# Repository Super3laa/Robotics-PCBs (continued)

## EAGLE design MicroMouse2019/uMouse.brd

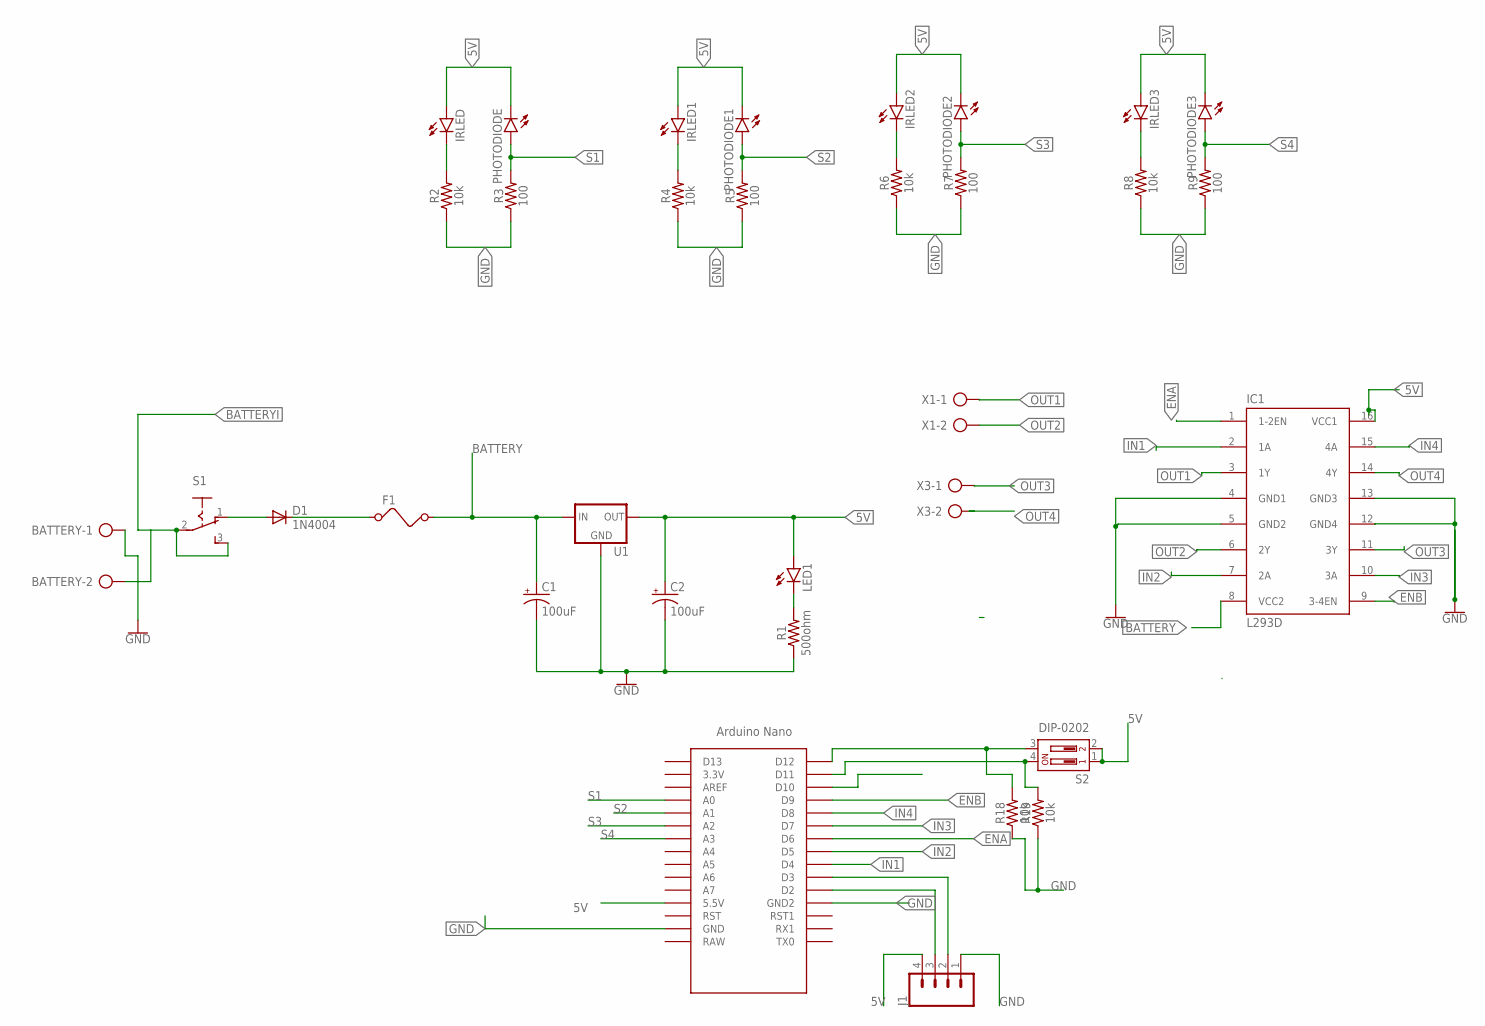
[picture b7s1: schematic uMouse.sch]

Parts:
BATTERY: AK500/2-H
C1, C2: 100uF; CPOL-RADIAL-2.5MM-6.5MM
D1: 1N4004; DO41-10
F1: FUSE
IC1: L293D; DIL16
IRLED, IRLED1, IRLED2, IRLED3: LED5MM
J1: CONN_04; 1X04
LED1: LED3MM
PHOTODIODE, PHOTODIODE1, PHOTODIODE2, PHOTODIODE3: LED5MM
R1: 500ohm; AXIAL-0.3
R2, R4, R6, R8, R18, R19: 10k; AXIAL-0.3
R3, R5, R7, R9: 100; AXIAL-0.3
S1: 255SB
S2: DIP-0202; DIPSWITCH-02
U1: 78XXS
U$2: NANO
X1, X3: AK500/2-H

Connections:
5V: C2.1 (+), IC1.16 (VCC1), IRLED.A, IRLED1.A, IRLED2.A, IRLED3.A, J1.4, LED1.A, PHOTODIODE.K (C), PHOTODIODE1.K (C), PHOTODIODE2.K (C), PHOTODIODE3.K (C), S2.1, S2.2, U1.OUT, U$2.5V (5.5V)
BATTERY: C1.1 (+), F1.2, IC1.8 (VCC2), U1.IN
BATTERYI: BATTERY.2, S1.2, S1.3 (S)
ENA: IC1.1 (1-2EN), U$2.D6
ENB: IC1.9 (3-4EN), U$2.D9
GND: BATTERY.1, C1.2 (-), C2.2 (-), IC1.4 (GND1), IC1.5 (GND2), IC1.12 (GND4), IC1.13 (GND3), J1.1, R1.P$1 (1), R2.P$1 (1), R3.P$1 (1), R4.P$1 (1), R5.P$1 (1), R6.P$1 (1), R7.P$1 (1), R8.P$1 (1), R9.P$1 (1), R18.P$1 (1), R19.P$1 (1), U1.GND, U$2.GND, U$2.GND1 (GND2)
IN1: IC1.2 (1A), U$2.D4
IN2: IC1.7 (2A), U$2.D5
IN3: IC1.10 (3A), U$2.D7
IN4: IC1.15 (4A), U$2.D8
unnamed: D1.A, S1.1 (O)
unnamed: D1.C, F1.1
unnamed: IRLED1.K (C), R4.P$2 (2)
unnamed: LED1.K (C), R1.P$2 (2)
unnamed: IRLED.K (C), R2.P$2 (2)
unnamed: R19.P$2 (2), S2.4, U$2.D11
unnamed: R18.P$2 (2), S2.3, U$2.D12
unnamed: IRLED2.K (C), R6.P$2 (2)
unnamed: IRLED3.K (C), R8.P$2 (2)
unnamed: J1.3, U$2.D2
unnamed: J1.2, U$2.D3
OUT1: IC1.3 (1Y), X1.1
OUT2: IC1.6 (2Y), X1.2
OUT3: IC1.11 (3Y), X3.1
OUT4: IC1.14 (4Y), X3.2
S1: PHOTODIODE.A, R3.P$2 (2), U$2.A0
S2: PHOTODIODE1.A, R5.P$2 (2), U$2.A1
S3: PHOTODIODE2.A, R7.P$2 (2), U$2.A2
S4: PHOTODIODE3.A, R9.P$2 (2), U$2.A3

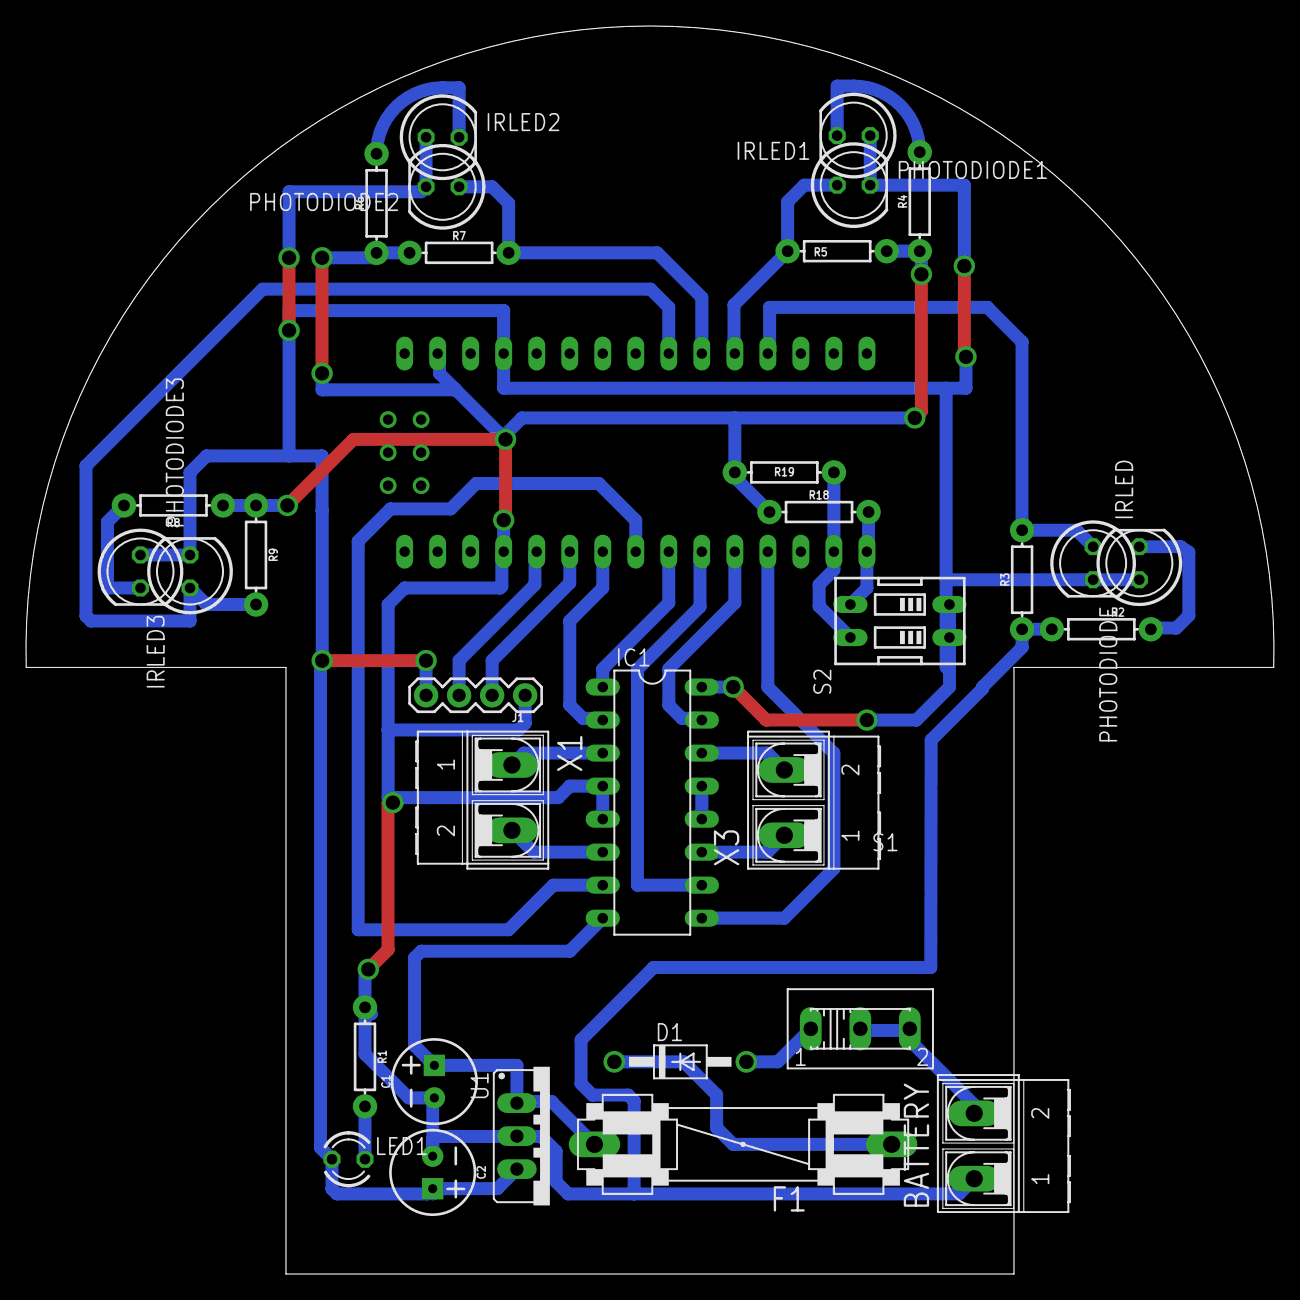
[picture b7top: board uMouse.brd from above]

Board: 2 copper layers, 96.0 x 96.0 mm, 33 parts (0 on the bottom side), 29 nets.

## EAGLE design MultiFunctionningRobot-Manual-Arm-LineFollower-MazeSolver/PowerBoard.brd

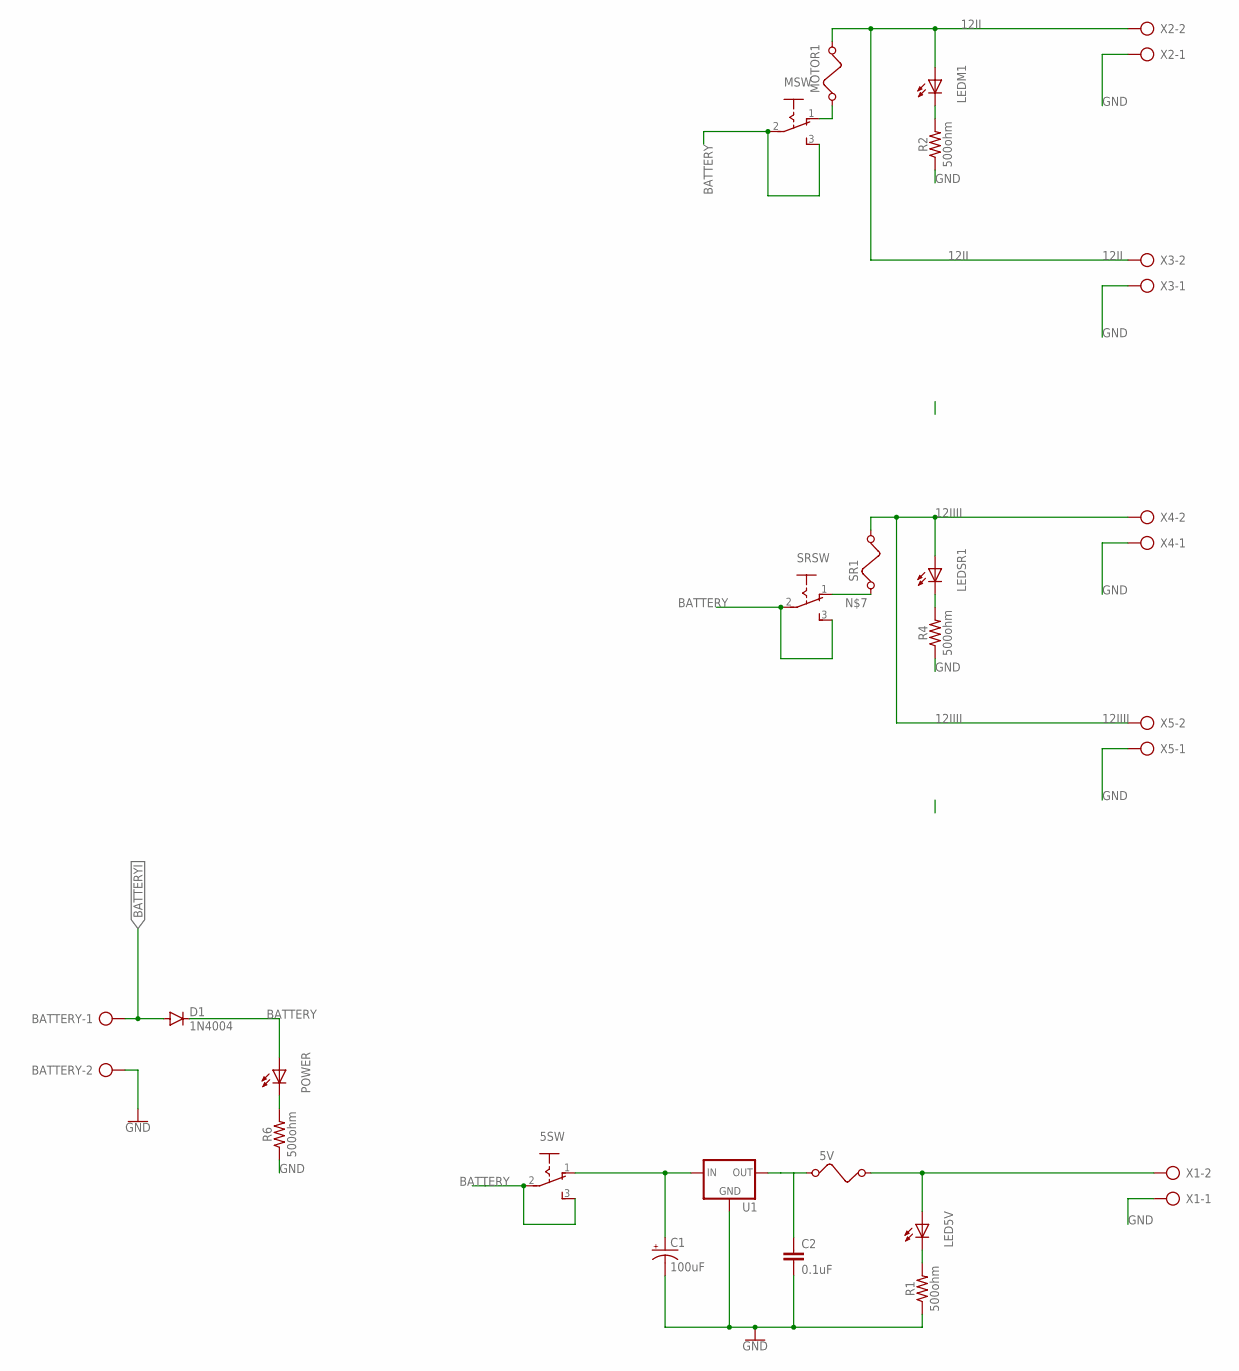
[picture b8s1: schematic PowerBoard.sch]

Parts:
5SW: 255SB
5V: FUSE
BATTERY: AK500/2-H
C1: 100uF; CPOL-RADIAL-2.5MM-6.5MM
C2: 0.1uF; CAP-PTH-SMALL-KIT
D1: 1N4004; DO41-10
LED5V: LED3MM
LEDM1: LED3MM
LEDSR1: LED3MM
MOTOR1: FUSE
MSW: 255SB
POWER: LED3MM
R1, R2, R4, R6: 500ohm; AXIAL-0.3
SR1: FUSE
SRSW: 255SB
U1: 78XXS
X1, X2, X3, X4, X5: AK500/2-H

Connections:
12II: LEDM1.A, MOTOR1.2, X2.2, X3.2
12IIII: LEDSR1.A, SR1.2, X4.2, X5.2
BATTERY: 5SW.2, 5SW.3 (S), D1.C, MSW.2, MSW.3 (S), POWER.A, SRSW.2, SRSW.3 (S)
BATTERYI: BATTERY.1, D1.A
GND: BATTERY.2, C1.2 (-), C2.2, R1.P$1 (1), R2.P$1 (1), R4.P$1 (1), R6.P$1 (1), U1.GND, X1.1, X2.1, X3.1, X4.1, X5.1
unnamed: POWER.K (C), R6.P$2 (2)
unnamed: LEDM1.K (C), R2.P$2 (2)
unnamed: LEDSR1.K (C), R4.P$2 (2)
unnamed: LED5V.K (C), R1.P$2 (2)
unnamed: SR1.1, SRSW.1 (O)
unnamed: MOTOR1.1, MSW.1 (O)
unnamed: 5V.1, C2.1, U1.OUT
unnamed: 5V.2, LED5V.A, X1.2
SSS: 5SW.1 (O), C1.1 (+), U1.IN

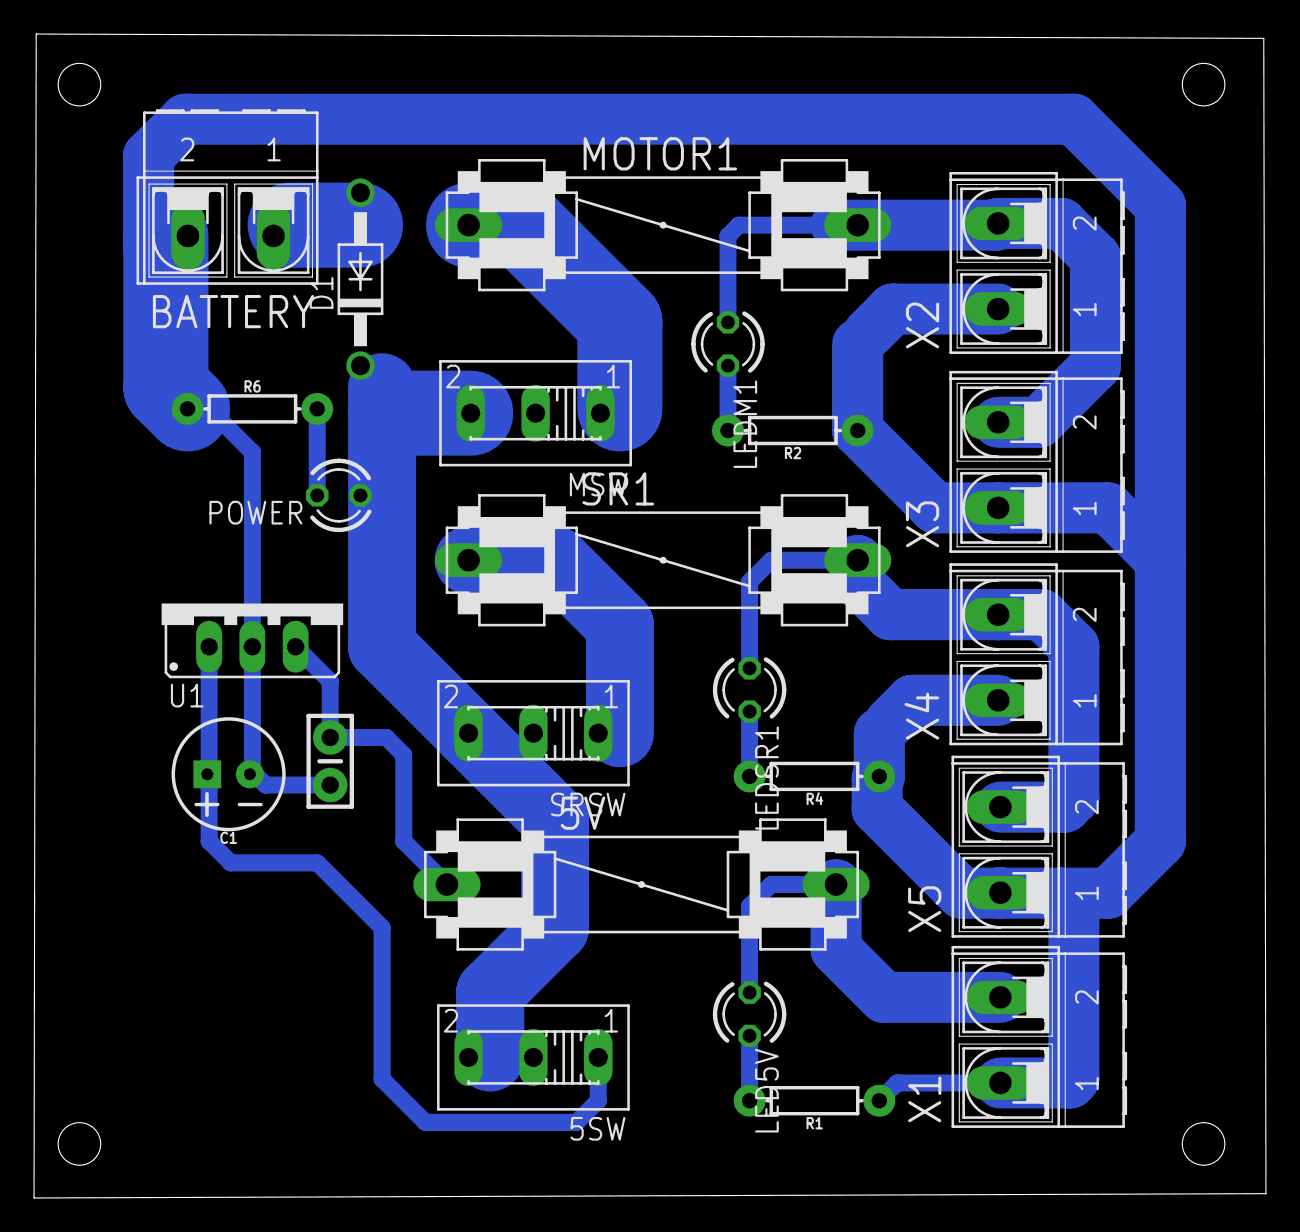
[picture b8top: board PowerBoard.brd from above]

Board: 2 copper layers, 72.4 x 68.4 mm, 24 parts (0 on the bottom side), 14 nets.

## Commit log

2020-03-12 Couple of Robotics PCBs
